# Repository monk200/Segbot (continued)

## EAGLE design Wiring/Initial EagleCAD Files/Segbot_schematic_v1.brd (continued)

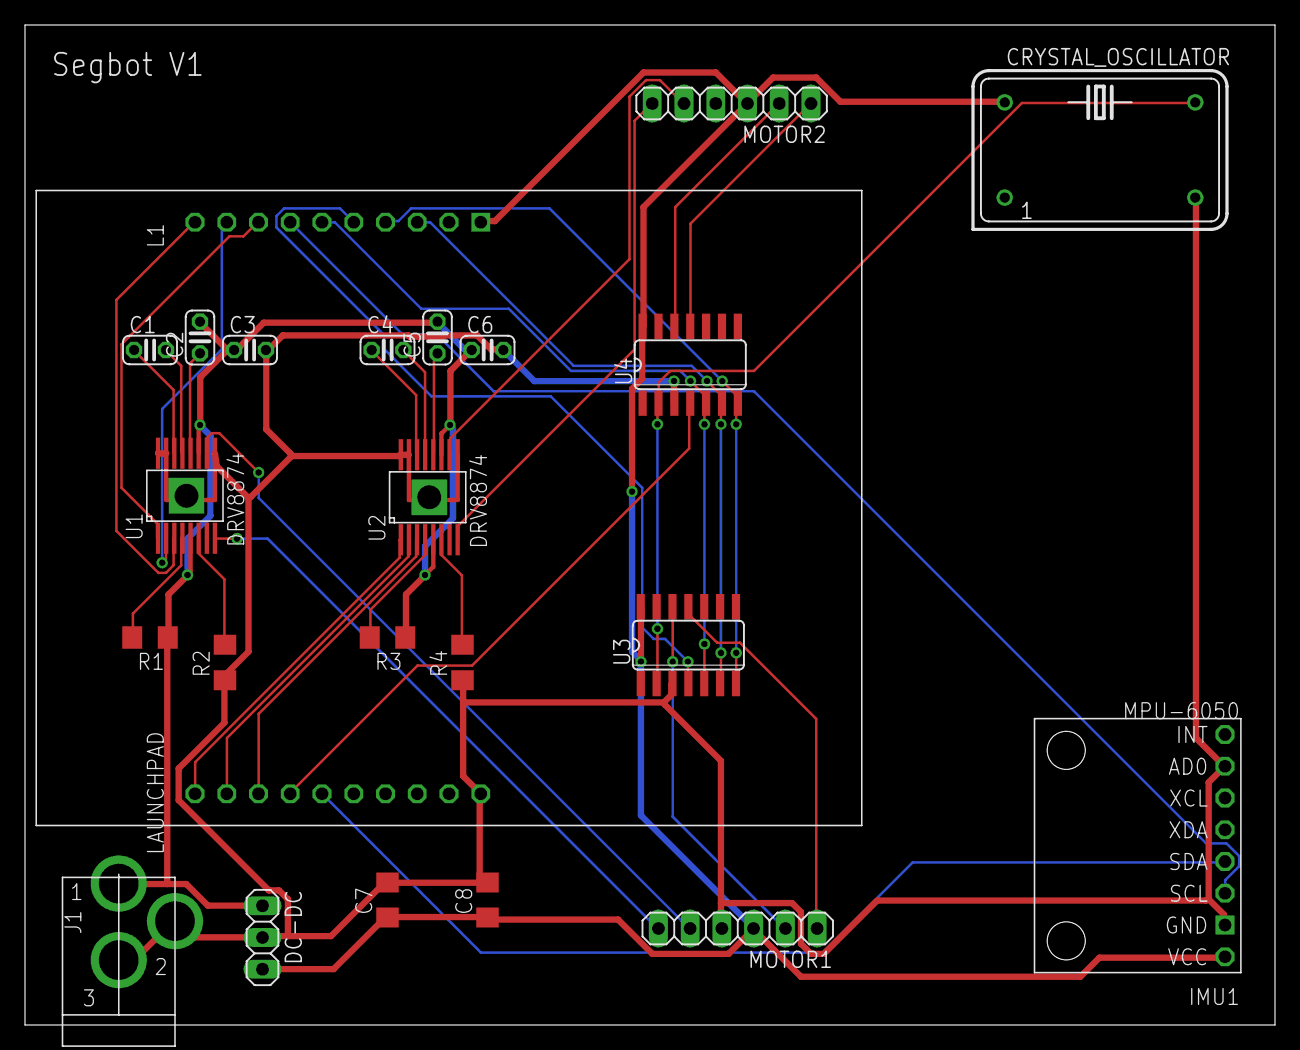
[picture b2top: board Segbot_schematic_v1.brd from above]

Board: 2 copper layers, 100.0 x 80.0 mm, 23 parts (0 on the bottom side), 35 nets.

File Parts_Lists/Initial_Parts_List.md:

# Parts List for the Initial Design
The first portion of this project initially allowed for the flexibility to design a Segbot of any size, but because I was intending to build it eventually I went in trying to pick cost-effective hobbyist parts. Below are details on the process of selecting each part.   

## Microcontroller
The original design was intended to use the MSP430G2553 microcontroller (on the TI development board) because it was used earlier in the course for homework projects and tinkering so it was a part I already owned and was familiar with. The MSP430 controller is a low-power, high-performance, 16-bit general purpose controller. This particular MSP430 chip has 512 bytes SRAM, 24 I/O pins, 8 ADC channels with 10 bit resoultion, and two 16-bit timers. Below is a simple pinout of the launchpad board used:  
<p align="center"><img src="http://embedded-lab.com/blog/wp-content/uploads/2017/08/MSP4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" alt="MSP430 Pinout" width="800"/></p>  

[Texas Instruments Page](https://www.ti.com/product/MSP430G2553#product-details##params)  
[Chip Datasheet](https://www.ti.com/lit/ds/symlink/msp430g2553.pdf)  
[Launchpad Datasheet](https://www.ti.com/lit/ug/slau772a/slau772a.pdf?ts=162121020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  
[Store page](https://www.digikey.com/en/products/detail/texas-instruments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  

Cost: $12 on digikey.com, $0 since I recieved it from the course  

## Motor Control
This was the first time I had experience choosing a motor and battery to begin creating a project (as opposed to having a starting kit). From the start, I knew I was searching for a 6-12V DC hobby motor because that was the kind of motors I've used before for robot car projects. Choosing a DC motor over an AC motor here is a no-brainer because AC motors need to be driven by AC current and tend to be used in stationary, high-load situations. Generally on my other robot cars, a 6V motor was sufficient but because of the added weight of the Segbot body it might be necessary to increase the voltage. Further calculations for this can be seen below, using estimated parameters from the rest of the Segbot build. Exploring other robot car kits and projects also led me to belive that the exact type of motor needed should be a micro gear reduction motor. Further research into why showed that often times DC motors rotate significantly faster than necessary for most applications and difficult to control, so adding the gearbox reduces the speed to a reasonable level and increases the motor's torque. Another consideration when choosing the motor is its compatibility with an optical encoder and wheels. Installing an optical encoder to a motor adds a more intensive task with notable room for error so immediately I took the luxury of not considering any motors that did not come pre-installed with an optical encoder. While browsing the remaining options, it was clear that I could also take the luxury of choosing a motor that also came with its own wheel. This continued to simplify my work because I didn't need to match up shaft sizes or be concerned about the width of the motor. Ultimately, the approach of getting the whole subassmbly together did make the final choice cheaper than the alternatives. The chosen motor subassembly was the Machifit 25GA370 DC 12V Micro Gear Reduction Motor and its details can be found below.  

<p align="center">
<img src="https://imgaz2.staticbg.com/thumb/large/oaupload/ser1/banggo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" alt="Motor Subassembly" width="200"/>
<img src="https://raw.githubusercontent.com/Arduinolibrary/DFRobot_12V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" alt="Encoder Pinout" width="400"/>
</p>  

[Store Page](https://www.banggood.com/Machifit-25GA370-DC-12V-Micro-Gear-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  
Cost: $40 for two motors  

An H-bridge is essential to be able to control the direction of the motor. The stall current of the chosen motor corresponds to the maximum continuous current the H-bridge needs to produce. The chosen motor's stall current is 1.8A so the H-bridge needs to have a peak output current that is sufficient. Searching [TI's selection of motor drivers](https://www.ti.com/motor-drivers/brushed-dc-bdc-drivers/over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 led to many seemingly suitable options. Because most students in the course were struggling selecting an H-bridge they could be confident would work, Prof. Block suggested a few options that he was familiar with and knew would work for different Segbot sizes. In my hobby-sized Segbot, he recommended the DRV8874.

[Chip Datasheet](https://www.ti.com/lit/ds/symlink/drv8874.pdf?ts=16212155138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  
[Texas Instruments Page](https://www.ti.com/product/DRV8874)  
Cost: $2.50 for two H-bridges  

## Sensors
Aside from the motor encoders, the only other sensors required for the balancing control are an accelerometer and gyroscope. This part was actually extremely easy to find because there is a popular Arduino module that combines both sensors, and since it's made for the Arduino it will also easily be able to be used with the MSP430. The module chosen was the MPU-6050:  

<p align="center"><img src="https://imgaz1.staticbg.com/thumb/large/upload/2012/jiangjun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" alt="Accelerometer and Gyroscope" width="200"/></p>  

[Chip Datasheet](http://myosuploads3.banggood.com/products/20190227/201902272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  
[Store page](https://www.banggood.com/Geekcreit-6DOF-MPU-6050-3-Axis-Gyro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  
Cost: $4  

## Battery
Again since I didn't have much experience determining what kind of battery a system needed, I was guided by Prof. Block to choose a lithium ion battery. He advised that it should have 2-3 cells and be rated for 1500-2500 mAh. The LiPo battery is ideal because it is lightweight and rechargable, even though it is important to be very careful to not short the leads. The battery I ended up choosing was specifically for hobby applications and its details are shown below:  

[Store page](https://www.amazon.com/Zeee-3000mAh-Connector-Airplane-Helic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  
Cost: $40 for two, though only one is needed  

Lastly, a DC-DC converter would be needed to scale the battery power down to power the MSP430. Since the battery chosen provides 11.1V and the MSP430 needs a 3.3V input, the chosen converter needs to fit that range. It was easy enough to find the OKI-78SR, with up to a 36V input and a 3.3V output:  

[Store page](https://www.digikey.com/en/products/detail/murata-power-solu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  
[Chip Datasheet](https://www.murata.com/products/productdata/8807037992990/ok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  
Cost: $4.50  

## Frame
Since I had free access to a 3D printer while in school, the body of the Segbot was planned to be 3D printed. This firstly creates an opportunity to work on my CAD skills and learn to use a 3D printer, but also allows the flexibility to create a custom-shaped body. More details can be found in the [CAD model]() section.  

Cost: $0

## Other Parts
A few parts needed for the assembly were provided by Prof. Block without detailed explanation. The first is the LS7366R Quadrature Counter, which is used to communicate with the MSP430's SPI. The other part is a crystal oscillator whose pinout was provided but specific part number was not. The connections between these parts and the controller's SPI peripheral can be seen on the last page of [this link](http://coecsl.ece.illinois.edu/ge423/LS7366CodeHandout.pdf). The first three pages contain the code needed to initialize the SPI on the microcontroller.  

[LS7366R Datasheet](https://lsicsi.com/datasheets/LS7366R.pdf)  

## Sources
https://www.powerelectric.com/motor-resources/motors101/what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  
https://www.engineersgarage.com/tech-articles/choosing-motor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  
https://rogershobbycenter.com/lipoguide

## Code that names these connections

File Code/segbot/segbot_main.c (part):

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uint16_t UARTPrint = 0;
uint32_t SPIB_isr_count = 0;
// joystick readings
float adcina2Volts = 0;  // ADCINA2 is connected to pin 29 = VRX = LR
float adcina3Volts = 0;  // ADCINA3 is connected to pin 26 = VRY = UD
// MPU-9250 readings
float accelXreading = 0, accelYreading = 0, accelZreading = 0;
float gyroXreading = 0, gyroYreading = 0, gyroZreading = 0;
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    // LED1 and PWM Pin
    GPIO_SetupPinMux(22, GPIO_MUX_CPU1, 0);
    GPIO_SetupPinOptions(22, GPIO_OUTPUT, GPIO_PUSHPULL);
    GpioDataRegs.GPACLEAR.bit.GPIO22 = 1;

    // LED2
    GPIO_SetupPinMux(52, GPIO_MUX_CPU1, 0);
    GPIO_SetupPinOptions(52, GPIO_OUTPUT, GPIO_PUSHPULL);
    GpioDataRegs.GPBCLEAR.bit.GPIO52 = 1;

    // LED3
    GPIO_SetupPinMux(67, GPIO_MUX_CPU1, 0);
    GPIO_SetupPinOptions(67, GPIO_OUTPUT, GPIO_PUSHPULL);
    GpioDataRegs.GPCCLEAR.bit.GPIO67 = 1;

    // LED4
    GPIO_SetupPinMux(94, GPIO_MUX_CPU1, 0);
    GPIO_SetupPinOptions(94, GPIO_OUTPUT, GPIO_PUSHPULL);
    GpioDataRegs.GPCCLEAR.bit.GPIO94 = 1;

    // LED5
    GPIO_SetupPinMux(95, GPIO_MUX_CPU1, 0);
    GPIO_SetupPinOptions(95, GPIO_OUTPUT, GPIO_PUSHPULL);
    GpioDataRegs.GPCCLEAR.bit.GPIO95 = 1;

    // LED6
    GPIO_SetupPinMux(97, GPIO_MUX_CPU1, 0);
    GPIO_SetupPinOptions(97, GPIO_OUTPUT, GPIO_PUSHPULL);
    GpioDataRegs.GPDCLEAR.bit.GPIO97 = 1;

    // LED7
    GPIO_SetupPinMux(111, GPIO_MUX_CPU1, 0);
    GPIO_SetupPinOptions(111, GPIO_OUTPUT, GPIO_PUSHPULL);
    GpioDataRegs.GPDCLEAR.bit.GPIO111 = 1;

    // LED8
    GPIO_SetupPinMux(130, GPIO_MUX_CPU1, 0);
    GPIO_SetupPinOptions(130, GPIO_OUTPUT, GPIO_PUSHPULL);
    GpioDataRegs.GPECLEAR.bit.GPIO130 = 1;

    // LED9
    GPIO_SetupPinMux(131, GPIO_MUX_CPU1, 0);
    GPIO_SetupPinOptions(131, GPIO_OUTPUT, GPIO_PUSHPULL);
    GpioDataRegs.GPECLEAR.bit.GPIO131 = 1;

    // LED10
    GPIO_SetupPinMux(4, GPIO_MUX_CPU1, 0);
    GPIO_SetupPinOptions(4, GPIO_OUTPUT, GPIO_PUSHPULL);
    GpioDataRegs.GPACLEAR.bit.GPIO4 = 1;

    // LED11
    GPIO_SetupPinMux(5, GPIO_MUX_CPU1, 0);
    GPIO_SetupPinOptions(5, GPIO_OUTPUT, GPIO_PUSHPULL);
    GpioDataRegs.GPACLEAR.bit.GPIO5 = 1;

    // LED12
    GPIO_SetupPinMux(6, GPIO_MUX_CPU1, 0);
    GPIO_SetupPinOptions(6, GPIO_OUTPUT, GPIO_PUSHPULL);
    GpioDataRegs.GPACLEAR.bit.GPIO6 = 1;

    // LED13
    GPIO_SetupPinMux(7, GPIO_MUX_CPU1, 0);
    GPIO_SetupPinOptions(7, GPIO_OUTPUT, GPIO_PUSHPULL);
    GpioDataRegs.GPACLEAR.bit.GPIO7 = 1;

    // LED14
    GPIO_SetupPinMux(8, GPIO_MUX_CPU1, 0);
    GPIO_SetupPinOptions(8, GPIO_OUTPUT, GPIO_PUSHPULL);
    GpioDataRegs.GPACLEAR.bit.GPIO8 = 1;

    // LED15
    GPIO_SetupPinMux(9, GPIO_MUX_CPU1, 0);
    GPIO_SetupPinOptions(9, GPIO_OUTPUT, GPIO_PUSHPULL);
    GpioDataRegs.GPACLEAR.bit.GPIO9 = 1;

    // LED16
    GPIO_SetupPinMux(24, GPIO_MUX_CPU1, 0);
    GPIO_SetupPinOptions(24, GPIO_OUTPUT, GPIO_PUSHPULL);
    GpioDataRegs.GPACLEAR.bit.GPIO24 = 1;

    // LED17
    GPIO_SetupPinMux(25, GPIO_MUX_CPU1, 0);
    GPIO_SetupPinOptions(25, GPIO_OUTPUT, GPIO_PUSHPULL);
    GpioDataRegs.GPACLEAR.bit.GPIO25 = 1;

    // LED18
    GPIO_SetupPinMux(26, GPIO_MUX_CPU1, 0);
    GPIO_SetupPinOptions(26, GPIO_OUTPUT, GPIO_PUSHPULL);
    GpioDataRegs.GPACLEAR.bit.GPIO26 = 1;

    // LED19
    GPIO_SetupPinMux(27, GPIO_MUX_CPU1, 0);
    GPIO_SetupPinOptions(27, GPIO_OUTPUT, GPIO_PUSHPULL);
    GpioDataRegs.GPACLEAR.bit.GPIO27 = 1;

    // LED20
    GPIO_SetupPinMux(60, GPIO_MUX_CPU1, 0);
    GPIO_SetupPinOptions(60, GPIO_OUTPUT, GPIO_PUSHPULL);
    GpioDataRegs.GPBCLEAR.bit.GPIO60 = 1;

    // LED21
    GPIO_SetupPinMux(61, GPIO_MUX_CPU1, 0);
    GPIO_SetupPinOptions(61, GPIO_OUTPUT, GPIO_PUSHPULL);
    GpioDataRegs.GPBCLEAR.bit.GPIO61 = 1;

    // LED22
    GPIO_SetupPinMux(157, GPIO_MUX_CPU1, 0);
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    //DRV8874 #1 DIR  Direction
    GPIO_SetupPinMux(29, GPIO_MUX_CPU1, 0);
    GPIO_SetupPinOptions(29, GPIO_OUTPUT, GPIO_PUSHPULL);
    GpioDataRegs.GPASET.bit.GPIO29 = 1;

    //DRV8874 #2 DIR  Direction
    GPIO_SetupPinMux(32, GPIO_MUX_CPU1, 0);
    GPIO_SetupPinOptions(32, GPIO_OUTPUT, GPIO_PUSHPULL);
    GpioDataRegs.GPBSET.bit.GPIO32 = 1;

    //MPU9250  CS  Chip Select
    GPIO_SetupPinMux(66, GPIO_MUX_CPU1, 0);
    GPIO_SetupPinOptions(66, GPIO_OUTPUT, GPIO_PUSHPULL);
    GpioDataRegs.GPCSET.bit.GPIO66 = 1;

    //PushButton 1
    GPIO_SetupPinMux(122, GPIO_MUX_CPU1, 0);
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    EPwm6Regs.AQCTLB.bit.ZRO = 0x2;
    EPwm6Regs.TBPHS.bit.TBPHS = 0;     // set phase to zero
    EDIS;
    GPIO_SetupPinMux(10, GPIO_MUX_CPU1, 1);     // set DRV1PWM from GPIO10 to EPWM6A
    GPIO_SetupPinMux(11, GPIO_MUX_CPU1, 1);     // set DRV2PWM from GPIO11 to EPWM6B

    EALLOW;
    GpioCtrlRegs.GPAPUD.bit.GPIO10 = 1;
    GpioCtrlRegs.GPAPUD.bit.GPIO11 = 1;
    EDIS;

    // Enable global Interrupts and higher priority real-time debug events
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    if (controleffort < -10) controleffort = -10;

    // there was an issue when testing my board where the motor's pinout was different on the right wheel so the code here for forward and backwards are swapped
    if (controleffort >= 0) GpioDataRegs.GPACLEAR.bit.GPIO29 = 1;    // if positive control effort, turn wheel forwards
    else GpioDataRegs.GPASET.bit.GPIO29 = 1;       // if negative control effort, turn wheel backwards

    EPwm6Regs.CMPA.bit.CMPA = (fabs(controleffort) /10.0) * EPwm6Regs.TBPRD;        // scales control effort to period and set for duty cycle
}
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    if (controleffort > 10) controleffort = 10;
    if (controleffort < -10) controleffort = -10;

    if (controleffort >= 0) GpioDataRegs.GPBSET.bit.GPIO32 = 1;    // if positive control effort, turn wheel forwards
    else GpioDataRegs.GPBCLEAR.bit.GPIO32 = 1;       // if negative control effort, turn wheel backwards

    EPwm6Regs.CMPB.bit.CMPB = (fabs(controleffort) /10.0) * EPwm6Regs.TBPRD;        // scales control effort to period and set for duty cycle
}
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
// ADCA hardware interrupt, called every 1ms
__interrupt void ADCA_ISR(void) {
    GpioDataRegs.GPBSET.bit.GPIO52 = 1;

    // JOYSTICK READINGS
    float adca2out = AdcaResultRegs.ADCRESULT0;       // ADCINA2 is connected to pin 29 = VRX = LR
    float adca3out = AdcaResultRegs.ADCRESULT1;       // ADCINA3 is connected to pin 26 = VRY = UD
    adcina2Volts = adca2out * (3.0/4095.0);
    adcina3Volts = adca3out * (3.0/4095.0);

    // IMU READINGS
    GpioDataRegs.GPCCLEAR.bit.GPIO66 = 1;       // GPIO66 low to act as slave select
    SpibRegs.SPIFFRX.bit.RXFFIL = 8;        // issue the SPIB_RX_INT when all values are in RX FIFO
    // get accel readings
    SpibRegs.SPITXBUF =  ((0x8000) | (0x3A00));      // read = 0x8000, register = 0x3A00 = INT_STATUS start
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    // CLEAR INTERRUPT FLAG
    AdcaRegs.ADCINTFLGCLR.bit.ADCINT1 = 1;
    PieCtrlRegs.PIEACK.all = PIEACK_GROUP1;
    GpioDataRegs.GPBCLEAR.bit.GPIO52 = 1;
}

// SPIB_RX interrupt
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    SPIB_isr_count++;

    // RECIEVE DATA
    GpioDataRegs.GPCSET.bit.GPIO66 = 1;     // deselect
    // read values
    int16_t temp = SpibRegs.SPIRXBUF;      // reads start for gyro
    int16_t accelXraw = SpibRegs.SPIRXBUF;      // reads full accel x
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
void setupSpib(void) {
    // Step 1 SPI SETUP ---------------------------------------------------------------------------------------------------
    GPIO_SetupPinMux(2, GPIO_MUX_CPU1, 0); // Set as GPIO2 and used as DAN777 SS
    GPIO_SetupPinOptions(2, GPIO_OUTPUT, GPIO_PUSHPULL); // Make GPIO2 an Output Pin
    GpioDataRegs.GPASET.bit.GPIO2 = 1; //Initially Set GPIO2/SS High so DAN777 is not selected
    GPIO_SetupPinMux(66, GPIO_MUX_CPU1, 0); // Set as GPIO66 and used as MPU-9250 SS
    GPIO_SetupPinOptions(66, GPIO_OUTPUT, GPIO_PUSHPULL); // Make GPIO66 an Output Pin
    GpioDataRegs.GPCSET.bit.GPIO66 = 1; //Initially Set GPIO66/SS High so MPU-9250 is not selected
    GPIO_SetupPinMux(63, GPIO_MUX_CPU1, 15); //Set GPIO63 pin to SPISIMOB
    GPIO_SetupPinMux(64, GPIO_MUX_CPU1, 15); //Set GPIO64 pin to SPISOMIB
    GPIO_SetupPinMux(65, GPIO_MUX_CPU1, 15); //Set GPIO65 pin to SPICLKB
    EALLOW;
    GpioCtrlRegs.GPBPUD.bit.GPIO63 = 0; // Enable Pull-ups on SPI PINs Recommended by TI for SPI Pins
    GpioCtrlRegs.GPCPUD.bit.GPIO64 = 0;
    GpioCtrlRegs.GPCPUD.bit.GPIO65 = 0;
    GpioCtrlRegs.GPBQSEL2.bit.GPIO63 = 3; // Set prequalifier for SPI PINS
    GpioCtrlRegs.GPCQSEL1.bit.GPIO64 = 3; // The prequalifier eliminates short noise spikes
    GpioCtrlRegs.GPCQSEL1.bit.GPIO65 = 3; // by making sure the serial pin stays low for 3 clock periods.
    EDIS;

    SpibRegs.SPICCR.bit.SPISWRESET = 0; // Put SPI in Reset
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    SpibRegs.SPIFFRX.bit.RXFFIL = 0x10; //Interrupt Level to 2 words or more received into FIFO causes interrupt

    // Step 2 Initialize MPU registers ---------------------------------------------------------------------------
    GpioDataRegs.GPCCLEAR.bit.GPIO66 = 1; // Slave Select Low

    // Perform the number of needed writes to SPITXBUF to write to all 13 registers
    SpibRegs.SPITXBUF = (0x1300 | 0x0000);       // To address 0x13 write 0x00
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
    // wait for the correct number of 16 bit values to be received into the RX FIFO
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
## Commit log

2021-05-17 Add initial parts list
2021-05-17 Fix formatting
2021-05-17 Update initial parts list
2021-05-17 Add initial wiring diagram
2021-05-17 Add links to initial parts list and wiring diagram
2021-05-17 Add initial EagleCAD and Fusion data
2021-05-17 Add initial EagleCAD screenshots
2021-05-17 Update images
2021-05-17 Update links in README
2021-05-17 Add simulations and reworked files
2021-05-17 Add links to README
2021-05-17 Fix video link
2021-05-17 Create parts list skeleton
2021-05-17 Update links
2021-05-18 Fix simulation link
2021-05-19 Add reworked wiring diagram and update matlab equations
2021-05-19 Add link
2021-05-19 Update reworked wiring
2021-05-19 Add TMS320F28379D pinout info
2021-05-19 Fill out details in parts list
2021-05-19 Add details about wiring considerations
2021-05-19 Add Matlab link
2021-05-19 Update wiring considerations
2021-05-19 Add code
2021-05-20 Create code walkthrough
2021-05-20 Add figures for control algorithms
2021-05-20 Add control algorithms to walkthrough
2021-05-20 Update video links
2021-05-20 Update README with results
2021-05-20 Fix video thumbnails
2021-05-20 Update video thumbnail
2021-05-20 Add labels to further analysis section
2021-05-20 Add demo video
2021-05-20 Add link to github video
2021-05-21 Add datasheets
2021-05-25 Add comments to Kalman filter
2021-05-25 Add Kalman sources
2021-05-25 Add demo picture
2021-05-25 Add final image to README
2021-05-25 Change image size
